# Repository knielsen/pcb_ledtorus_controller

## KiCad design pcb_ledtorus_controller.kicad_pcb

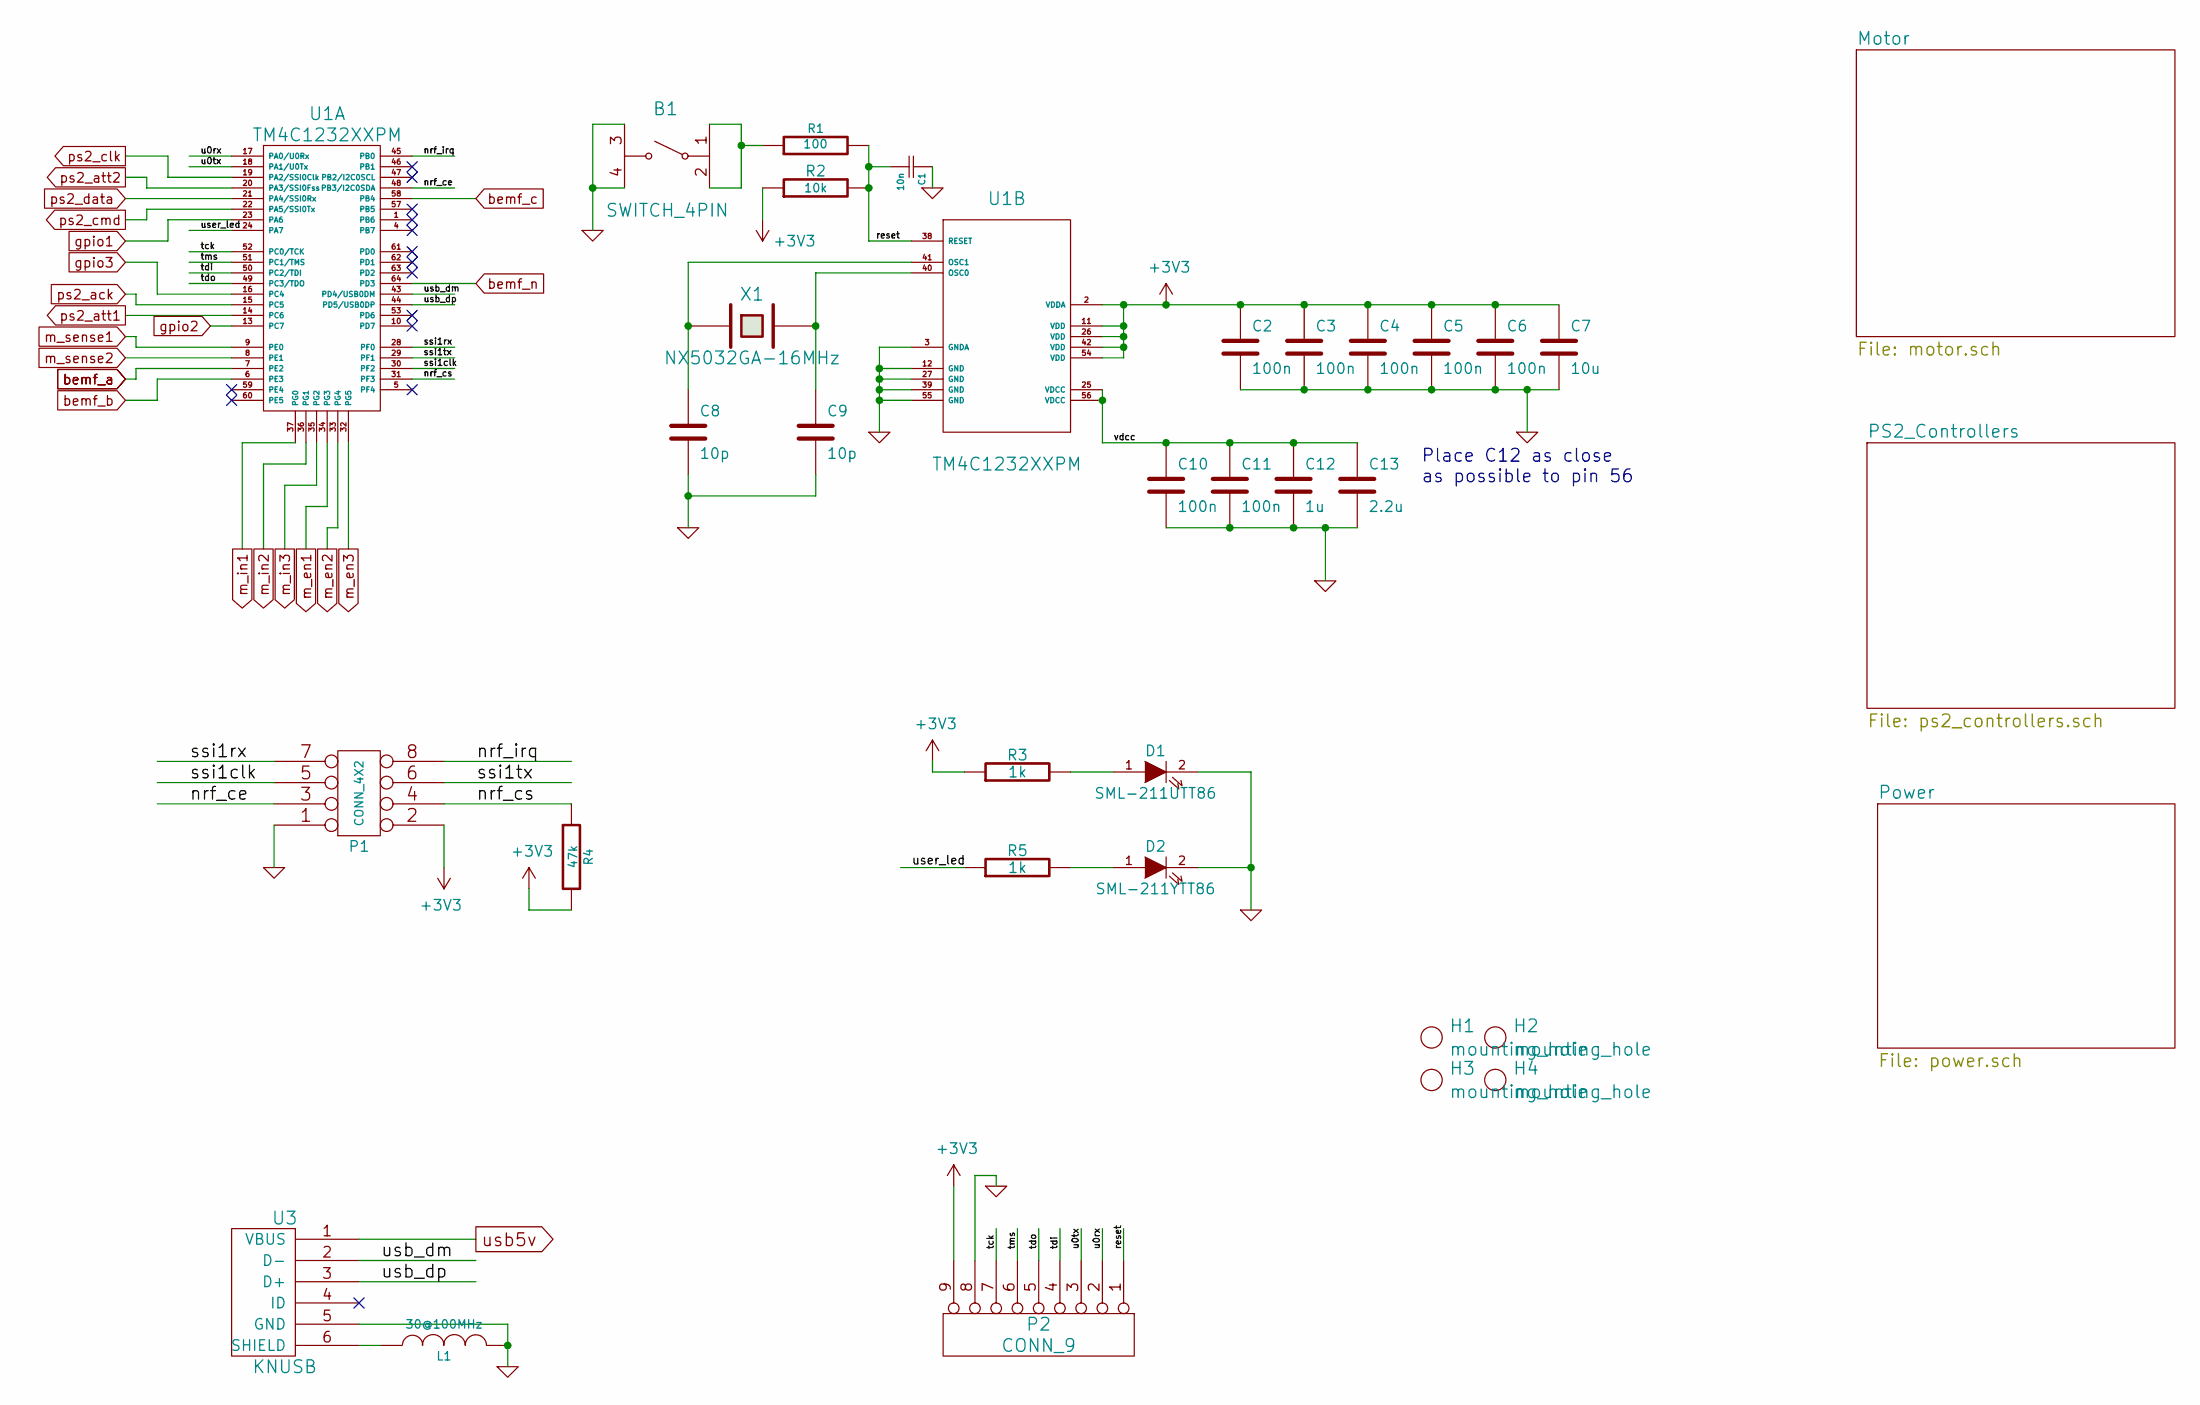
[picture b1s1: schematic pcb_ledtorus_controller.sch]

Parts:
B1: SWITCH_4PIN; SWITCH_FSMJSMA
C1: 10n; C_0805
C2, C3, C4, C5, C6, C10, C11: 100n; C_0603
C7: 10u; C_0805
C8, C9: 10p; C_0805
C12: 1u; C_0805
C13: 2.2u; C_0805
D1: SML-211UTT86; LED_0805
D2: SML-211YTT86; LED_0805
H1, H2, H3, H4: mounting_hole; MountingHole_4.3mm_M4
L1: 30@100MHz; L_0603
P1: CONN_4X2; Pin_Header_Straight_2x04_Pitch2.54mm
P2: CONN_9; Pin_Header_Straight_1x09_Pitch2.54mm
R1: 100; R_0805
R2: 10k; R_0805
R3, R5: 1k; R_0805
R4: 47k; R_0805
U1: TM4C1232XXPM; LQFP_64
U3: KNUSB; 10103594-0001LF
X1: NX5032GA-16MHz; NX5032GA

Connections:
+3V3: C2.1, C3.1, C4.1, C5.1, C6.1, C7.1, P1.2, P2.9, R2.1, R3.1, R4.2, U1.2 (VDDA), U1.11 (VDD), U1.26 (VDD), U1.42 (VDD), U1.54 (VDD); also elsewhere on the board
/nrf_ce: P1.3, U1.48 (PB3/I2C0SDA)
/nrf_cs: P1.4, R4.1, U1.31 (PF3)
/nrf_irq: P1.8, U1.45 (PB0)
/reset: C1.2, P2.1, R1.2, R2.2, U1.38 (RESET)
/ssi1clk: P1.5, U1.30 (PF2)
/ssi1rx: P1.7, U1.28 (PF0)
/ssi1tx: P1.6, U1.29 (PF1)
/tck: P2.7, U1.52 (PC0/TCK)
/tdi: P2.4, U1.50 (PC2/TDI)
/tdo: P2.5, U1.49 (PC3/TDO)
/tms: P2.6, U1.51 (PC1/TMS)
/u0rx: P2.2, U1.17 (PA0/U0Rx)
/u0tx: P2.3, U1.18 (PA1/U0Tx)
/usb_dm: U1.43 (PD4/USB0DM), U3.2 (D-)
/usb_dp: U1.44 (PD5/USB0DP), U3.3 (D+)
/user_led: R5.1, U1.24 (PA7)
/vdcc: C10.1, C11.1, C12.1, C13.1, U1.25 (VDCC), U1.56 (VDCC)
GND: B1.3, B1.4, C1.1, C2.2, C3.2, C4.2, C5.2, C6.2, C7.2, C8.2, C9.2, C10.2, C11.2, C12.2, C13.2, D1.2 (K), D2.2 (K), L1.2, P1.1, P2.8, U1.3 (GNDA), U1.12 (GND), U1.27 (GND), U1.39 (GND), U1.55 (GND), U3.5 (GND); also elsewhere on the board
unnamed: B1.1, B1.2, R1.1
unnamed: C8.1, U1.41 (OSC1), X1.1
unnamed: C9.1, U1.40 (OSC0), X1.2
unnamed: D1.1 (A), R3.2
unnamed: D2.1 (A), R5.2
unnamed: L1.1, U3.6 (SHIELD)
bemf_a: U1.7 (PE2); also elsewhere on the board
bemf_b: U1.6 (PE3); also elsewhere on the board
bemf_c: U1.58 (PB4); also elsewhere on the board
bemf_n: U1.64 (PD3); also elsewhere on the board
gpio1: U1.23 (PA6); also elsewhere on the board
gpio2: U1.13 (PC7); also elsewhere on the board
gpio3: U1.16 (PC4); also elsewhere on the board
m_en1: U1.34 (PG3); also elsewhere on the board
m_en2: U1.33 (PG4); also elsewhere on the board
m_en3: U1.32 (PG5); also elsewhere on the board
m_in1: U1.37 (PG0); also elsewhere on the board
m_in2: U1.36 (PG1); also elsewhere on the board
m_in3: U1.35 (PG2); also elsewhere on the board
m_sense1: U1.9 (PE0); also elsewhere on the board
m_sense2: U1.8 (PE1); also elsewhere on the board
ps2_ack: U1.15 (PC5); also elsewhere on the board
ps2_att1: U1.14 (PC6); also elsewhere on the board
ps2_att2: U1.20 (PA3/SSI0Fss); also elsewhere on the board
ps2_clk: U1.19 (PA2/SSI0Clk); also elsewhere on the board
ps2_cmd: U1.22 (PA5/SSI0Tx); also elsewhere on the board
ps2_data: U1.21 (PA4/SSI0Rx); also elsewhere on the board
usb5v: U3.1 (VBUS); also elsewhere on the board

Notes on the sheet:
Place C12 as close as possible to pin 56

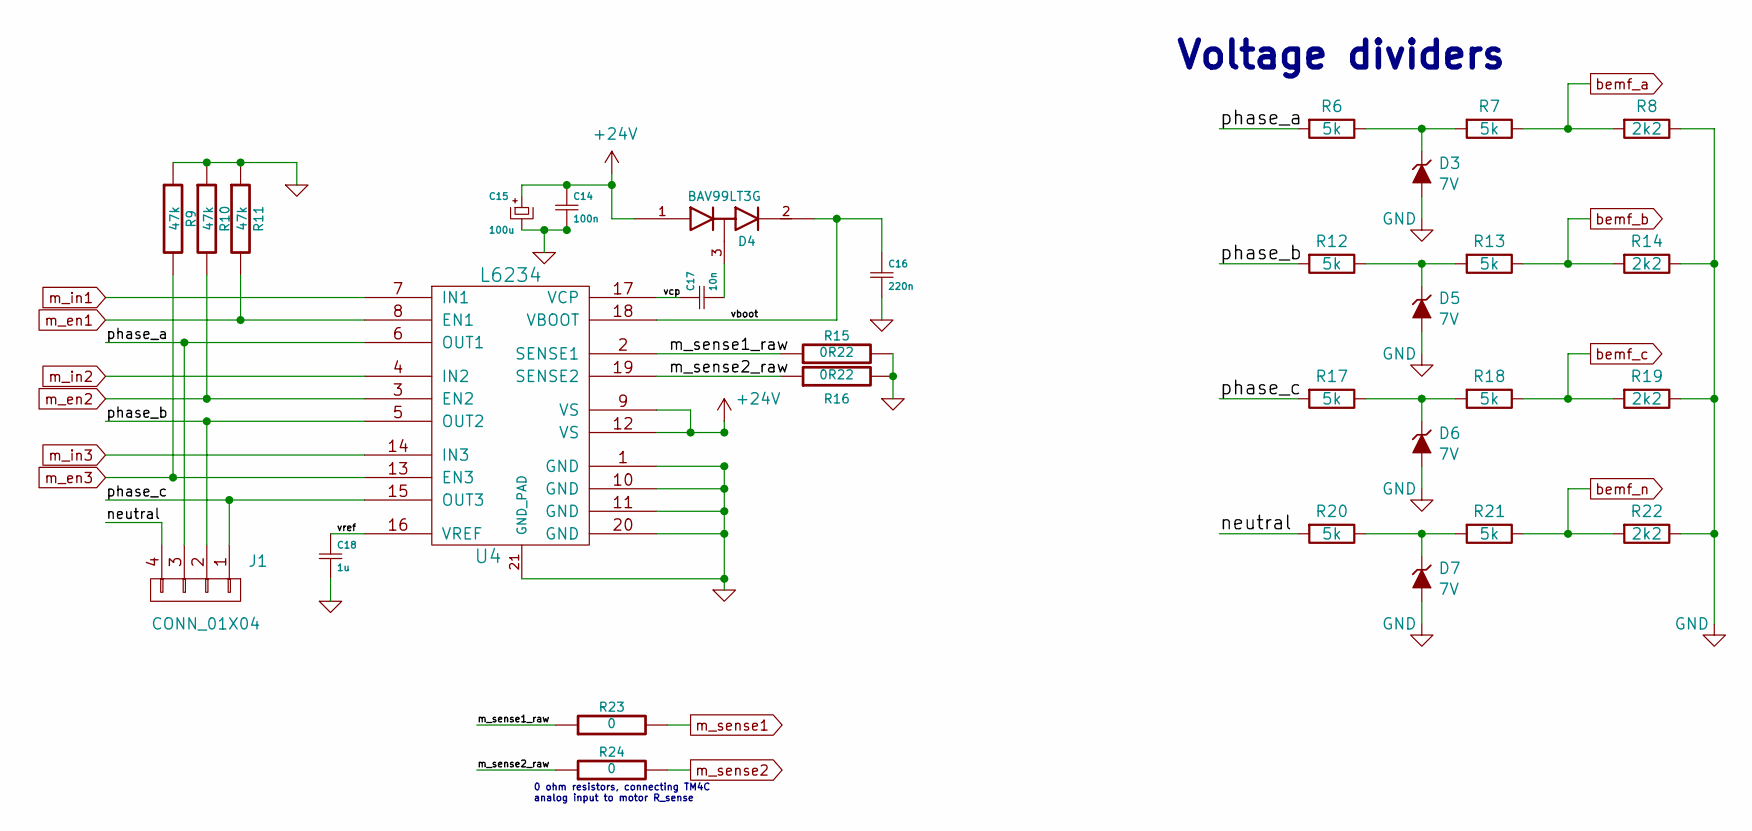
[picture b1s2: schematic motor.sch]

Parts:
C14: 100n; C_0603
C15: 100u; c_elec_6.3x7.7
C16: 220n; C_0805
C17: 10n; C_0805
C18: 1u; C_0805
D3, D5, D6, D7: 7V; D_SOD-123
D4: BAV99LT3G; SOT-23
J1: CONN_01X04; Pin_Header_Straight_1x04_Pitch2.54mm
R6, R7, R12, R13, R17, R18, R20, R21: 5k; R_0603
R8, R14, R19, R22: 2k2; R_0603
R9, R10, R11: 47k; R_0805
R15, R16: 0R22; R_0805
R23, R24: 0; R_0805
U4: L6234; POWERSO20_stencil

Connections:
+24V: C14.1, C15.1, D4.1 (Anode), U4.9 (VS), U4.12 (VS); also elsewhere on the board
/Motor/m_sense1_raw: R15.1, R23.1, U4.2 (SENSE1)
/Motor/m_sense2_raw: R16.1, R24.1, U4.19 (SENSE2)
/Motor/neutral: J1.4, R20.2
/Motor/phase_a: J1.3, R6.2, U4.6 (OUT1)
/Motor/phase_b: J1.2, R12.2, U4.5 (OUT2)
/Motor/phase_c: J1.1, R17.2, U4.15 (OUT3)
/Motor/vboot: C16.1, D4.2 (cathode), U4.18 (VBOOT)
/Motor/vcp: C17.1, U4.17 (VCP)
/Motor/vref: C18.1, U4.16 (VREF)
GND: C14.2, C15.2, C16.2, C18.2, D3.2 (A), D5.2 (A), D6.2 (A), D7.2 (A), R8.1, R9.1, R10.1, R11.1, R14.1, R15.2, R16.2, R19.1, R22.1, U4.1 (GND), U4.10 (GND), U4.11 (GND), U4.20 (GND), U4.21 (GND_PAD); also elsewhere on the board
unnamed: C17.2, D4.3 (AK)
unnamed: D3.1 (K), R6.1, R7.2
unnamed: D5.1 (K), R12.1, R13.2
unnamed: D6.1 (K), R17.1, R18.2
unnamed: D7.1 (K), R20.1, R21.2
bemf_a: R7.1, R8.2; also elsewhere on the board
bemf_b: R13.1, R14.2; also elsewhere on the board
bemf_c: R18.1, R19.2; also elsewhere on the board
bemf_n: R21.1, R22.2; also elsewhere on the board
m_en1: R11.2, U4.8 (EN1); also elsewhere on the board
m_en2: R10.2, U4.3 (EN2); also elsewhere on the board
m_en3: R9.2, U4.13 (EN3); also elsewhere on the board
m_in1: U4.7 (IN1); also elsewhere on the board
m_in2: U4.4 (IN2); also elsewhere on the board
m_in3: U4.14 (IN3); also elsewhere on the board
m_sense1: R23.2; also elsewhere on the board
m_sense2: R24.2; also elsewhere on the board

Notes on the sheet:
0 ohm resistors, connecting TM4C analog input to motor R_sense
Voltage dividers

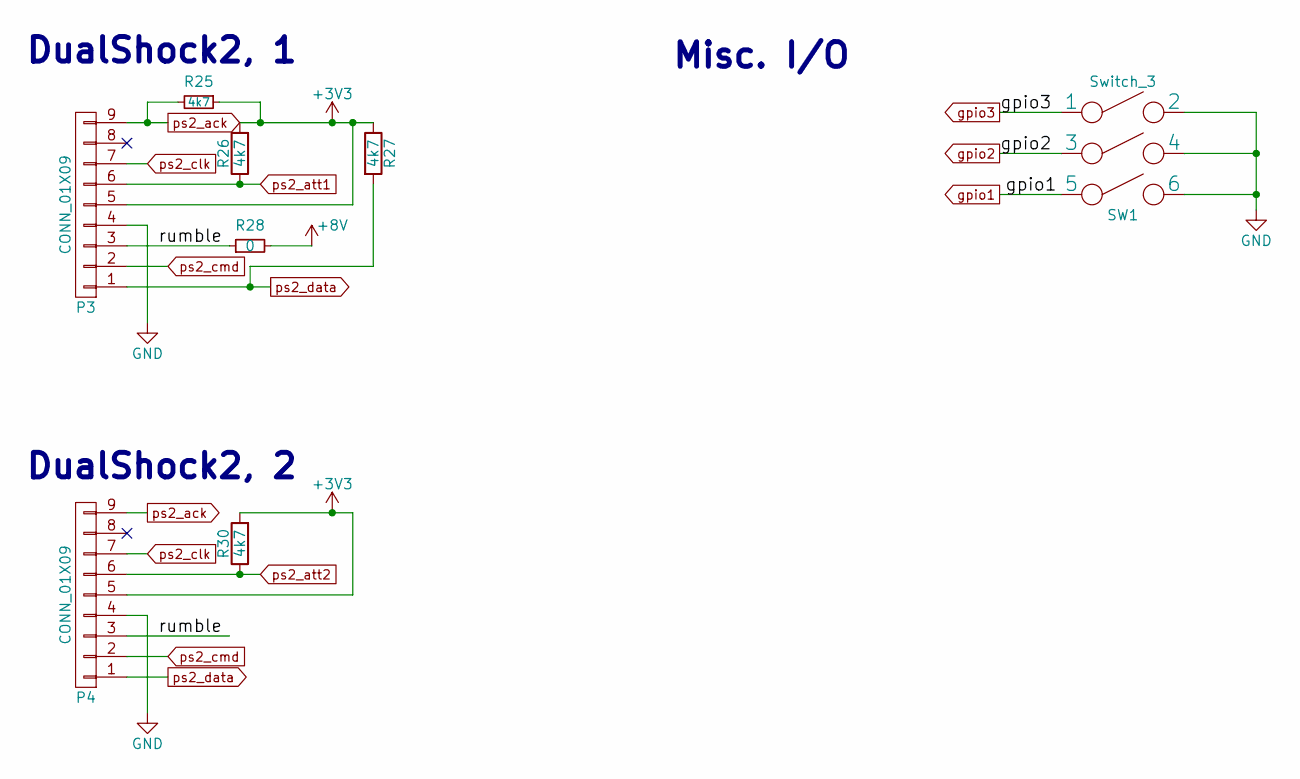
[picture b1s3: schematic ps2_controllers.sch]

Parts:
P3, P4: CONN_01X09; DualShock_conn
R25, R26, R27, R30: 4k7; R_0603
R28: 0; R_0805
SW1: Switch_3; DIPSWITCH_X3

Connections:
+3V3: P3.5, P4.5, R25.1, R26.2, R27.1, R30.2; also elsewhere on the board
+8V: R28.2; also elsewhere on the board
/PS2_Controllers/rumble: P3.3, P4.3, R28.1
GND: P3.4, P4.4, SW1.2, SW1.4, SW1.6; also elsewhere on the board
gpio1: SW1.5; also elsewhere on the board
gpio2: SW1.3; also elsewhere on the board
gpio3: SW1.1; also elsewhere on the board
ps2_ack: P3.9, P4.9, R25.2; also elsewhere on the board
ps2_att1: P3.6, R26.1; also elsewhere on the board
ps2_att2: P4.6, R30.1; also elsewhere on the board
ps2_clk: P3.7, P4.7; also elsewhere on the board
ps2_cmd: P3.2, P4.2; also elsewhere on the board
ps2_data: P3.1, P4.1, R27.2; also elsewhere on the board

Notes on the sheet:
DualShock2, 1
DualShock2, 2
Misc. I/O

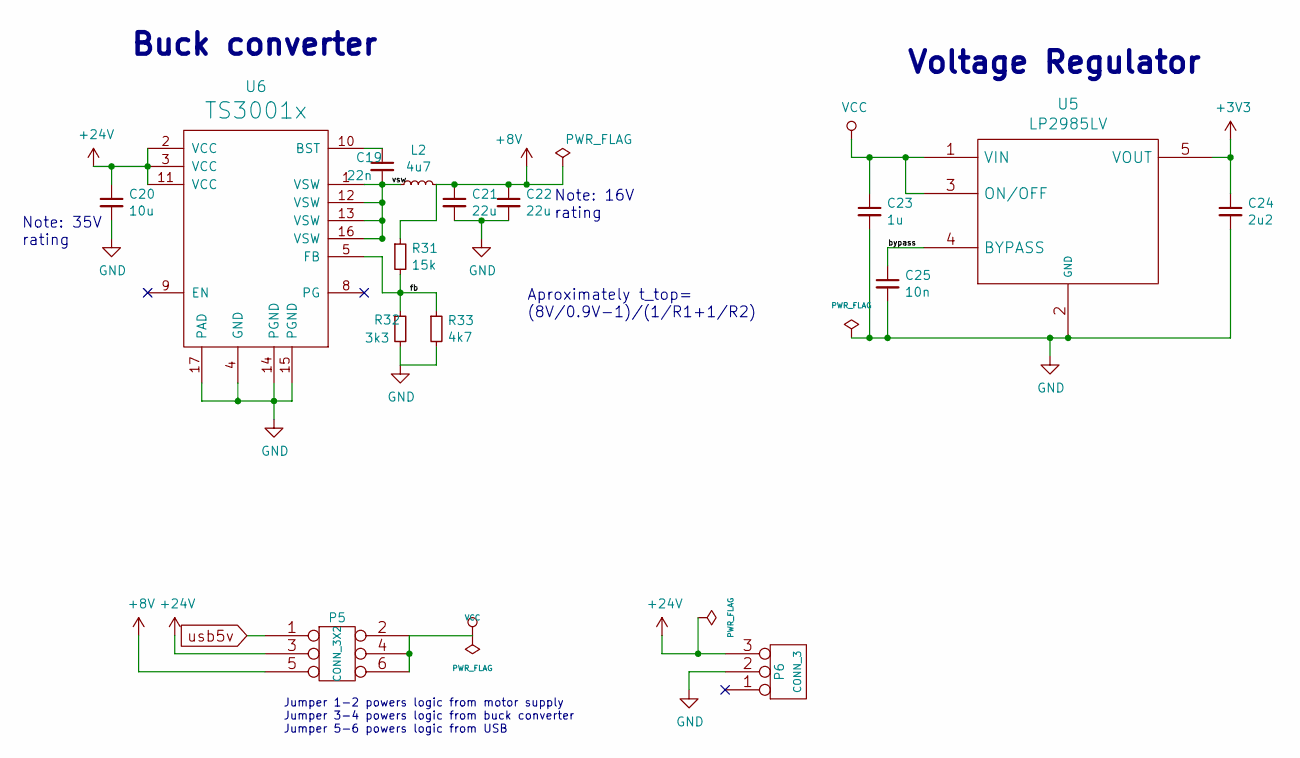
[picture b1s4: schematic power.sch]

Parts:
C19: 22n; C_0603
C20: 10u; C_0805
C21, C22: 22u; C_0805
C23: 1u; C_0805
C24: 2u2; C_0805
C25: 10n; C_0805
L2: 4u7; Coil_WE_7447786004
P5: CONN_3X2; Pin_Header_Straight_2x03_Pitch2.54mm
P6: CONN_3; dc_socket
R31: 15k; R_0603
R32: 3k3; R_0603
R33: 4k7; R_0603
U5: LP2985LV; SOT-23-5
U6: TS3001x; QFN16-TS30001

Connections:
+3V3: C24.1, U5.5 (VOUT); also elsewhere on the board
+8V: C21.1, C22.1, L2.2, P5.5, R31.1; also elsewhere on the board
+24V: C20.1, P5.3, P6.3, U6.2 (VCC), U6.3 (VCC), U6.11 (VCC); also elsewhere on the board
/Power/bypass: C25.1, U5.4 (BYPASS)
/Power/fb: R31.2, R32.1, R33.1, U6.5 (FB)
/Power/vsw: C19.2, L2.1, U6.1 (VSW), U6.12 (VSW), U6.13 (VSW), U6.16 (VSW)
GND: C20.2, C21.2, C22.2, C23.2, C24.2, C25.2, P6.2 (PM), R32.2, R33.2, U5.2 (GND), U6.4 (GND), U6.14 (PGND), U6.15 (PGND), U6.17 (PAD); also elsewhere on the board
unnamed: C19.1, U6.10 (BST)
VCC: C23.1, P5.2, P5.4, P5.6, U5.1 (VIN), U5.3 (ON/OFF)
usb5v: P5.1; also elsewhere on the board

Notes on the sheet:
Note: 35V rating
Note: 16V rating
Aproximately t_top= (8V/0.9V-1)/(1/R1+1/R2)
Jumper 1-2 powers logic from motor supply Jumper 3-4 powers logic from buck converter Jumper 5-6 powers logic from USB
Voltage Regulator
Buck converter

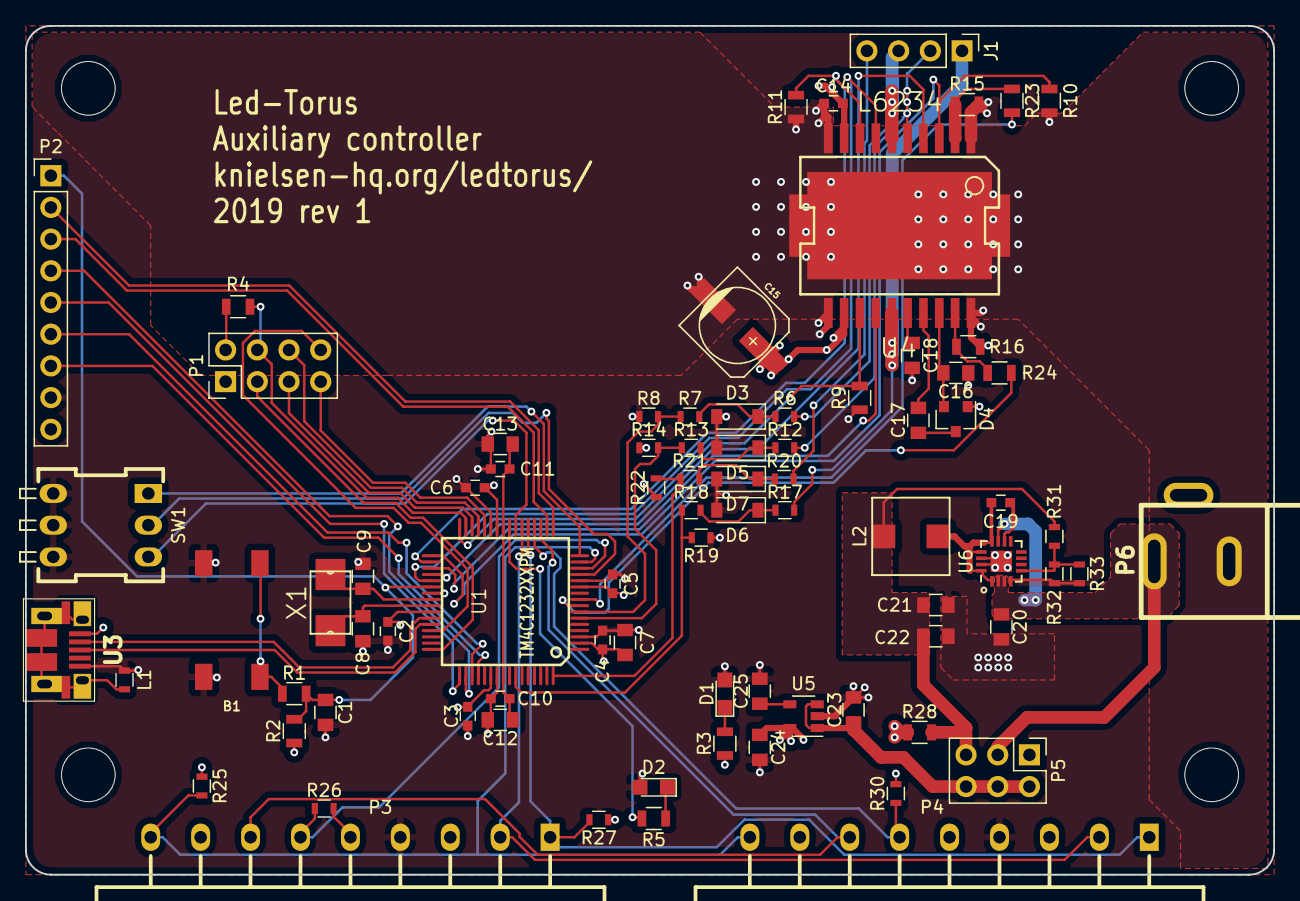
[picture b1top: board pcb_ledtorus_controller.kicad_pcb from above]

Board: 4 copper layers, 100.0 x 68.0 mm, 85 parts (0 on the bottom side), 69 nets.

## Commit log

2018-12-29 Partial steps towards a new controller PCB for the LED-torus
2018-12-29 Passing ERC
2018-12-29 Starting on netlist
2018-12-30 Work on layout
2019-03-04 Initial routing complete
2019-03-17 Completing cleanups and ToDos:
    - L6234 thermal vias done
    - Gerbers checked
    - Misc. io and stuff tweaks
2019-06-02 Submitted rev1 for production @ SeeedStudio
